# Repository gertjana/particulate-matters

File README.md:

# Particulate Matter Bike Monitor

This project is a mobile air quality monitoring system designed to be mounted on a bicycle. It measures fine particulate matter (PM1, PM2.5, and PM10) and records GPS location data during your commute. The collected data is stored locally on an SD card and displayed in real-time on an OLED screen, enabling you to create heatmaps of air pollution along your cycling routes.

## Features

- **Real-time air quality monitoring:** Measures PM1, PM2.5, and PM10 concentrations using the BMV080 particulate matter sensor.
- **GPS tracking:** Captures latitude, longitude, and timestamp for each measurement.
- **Local data storage:** Saves measurements to SD card with date-based file organization.
- **Real-time display:** Shows current readings and GPS coordinates on an OLED display.
- **Sensor health monitoring:** Detects when the sensor is obstructed and displays warnings.

## Hardware Requirements

- Arduino-compatible board (ESP32 recommended for SD card support)
- BMV080 Particulate Matter Sensor (I2C)
- GPS module (compatible with TinyGPS++)
- OLED Display (SSD1306, 128x32)
- SD Card Module (SPI)
- Battery pack
- Bicycle mounting hardware

## Pin Configuration

- **I2C (Wire):** SDA, SCL - for BMV080 sensor and OLED display
- **SPI (SD Card):** CS:44, MOSI:9, MISO:8, CLK:7
- **GPS (Software Serial):** TX:3, RX:2

## System Architecture

The system operates on a 10-second measurement interval and includes:

1. **Data Collection:** Reads PM1, PM2.5, PM10, and GPS coordinates
2. **Data Processing:** Packages data into JSON format
3. **Local Storage:** Saves to SD card with date-based filenames
4. **Real-time Display:** Shows current readings on OLED screen

## Data Format

Each measurement is stored as a JSON object with the following structure:

```json
{
  "pm": {
    "pm1": 15,
    "pm2.5": 25,
    "pm10": 45,
    "obstructed": false
  },
  "gps": {
    "date": "15-12-2024",
    "time": "14:30:25",
    "latitude": "52.12345678",
    "longitude": "4.87654321"
  }
}
```

## File Organization

Data is stored on the SD card with the following structure:

- Files are named by date: `DD-MM-YYYY.txt`
- Each line contains one JSON measurement
- Files are created automatically when data is available

## Setup

1. Clone this repository.
2. Install required libraries:
   - SparkFun_BMV080_Arduino_Library
   - TinyGPSPlus
   - ArduinoJson
   - Adafruit_GFX
   - Adafruit_SSD1306
3. Connect hardware according to pin configuration
4. Insert formatted SD card
5. Upload `dust_sensor_new/dust_sensor_new.ino` to your Arduino board
6. Mount the device on your bike and power it up before your ride

## Debug Mode

The system includes comprehensive debug output when `DEBUG` is defined. This includes:

- SD card information (type, size, free space)
- Sensor initialization status
- GPS data processing
- File writing operations

To enable debug mode, ensure `#define DEBUG` is uncommented in the code.

## Data Analysis

### Local Analysis

- Data files can be read directly from the SD card
- JSON format makes it easy to parse with any programming language
- Each measurement includes timestamp and location data

### Heatmap Generation

For setting up and using the heatmap visualization, see [heatmap/README.md](heatmap/README.md)

See [`example.md`](example.md) for sample data format and structure.

## License

MIT License

## Contributing

Contributions are welcome! Please open an issue or submit a pull request.

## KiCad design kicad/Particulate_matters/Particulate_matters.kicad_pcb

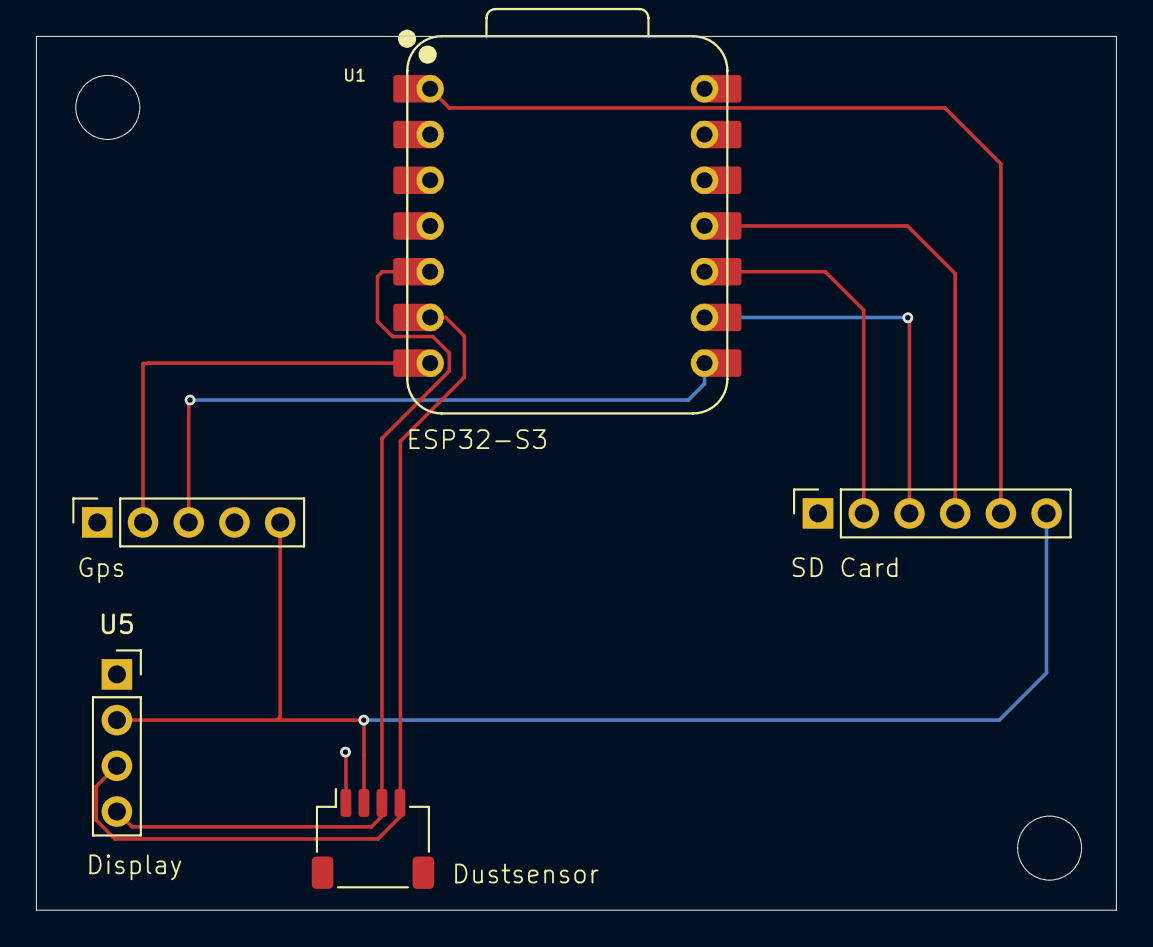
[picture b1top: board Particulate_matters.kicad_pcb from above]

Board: 2 copper layers, 60.0 x 48.5 mm, 5 parts (0 on the bottom side), 10 nets.

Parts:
U1: XIAO-ESP32-S3-DIP; XIAO-ESP32S3-DIP
U2: PinSocket_1x05_P2.54mm_Vertical
U3: JST_SH_SM04B-SRSS-TB_1x04-1MP_P1.00mm_Horizontal
U4: PinSocket_1x06_P2.54mm_Vertical
U5: PinSocket_1x04_P2.54mm_Vertical

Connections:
GND: U1.13 (GND), U2.4 (GND), U3.1 (GND), U4.1 (GND), U5.1 (GND)
unnamed: U1.1 (GPIO1/D0/A0), U4.5 (CS)
unnamed: U1.5 (GPIO5/D4/I2C_SDA), U3.3 (SDA), U5.4 (SDA)
unnamed: U1.9 (GPIO7/D8/A8/SCK), U4.3 (CLK)
unnamed: U1.10 (GPIO8/D9/A9/MISO), U4.2 (MISO)
unnamed: U1.6 (GPIO9/D5/I2C_SCL), U3.4 (SDL), U5.3 (SCK)
unnamed: U1.11 (GPIO9/D10/A10/MOSI), U4.4 (MOSI)
unnamed: U1.8 (U0RXD/D7/RX), U2.3 (TX)
unnamed: U1.7 (U0TXD/D6/TX), U2.2 (RX)
VCC: U1.12 (VCC_3V3), U2.5 (VCC), U3.2 (VCC), U4.6 (3V3), U5.2 (VCC)

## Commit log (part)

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2018-02-22 Arduino sketch to send ppd42 sensor data through lora
2018-03-11 added an gps module
2018-03-19 year is 2 bytes
2025-05-28 updated for new TTN Application and moved sensitive values out of the source
2025-06-02 All big endian now, added formatter to turn the data into json, and a markdown file describing the format
2025-06-03 Added altitude to the message instead of the centisecond
2025-06-03 Added temperature
2025-06-04 Removed Temperature, it was not needed in the calculations and took too much space in the box
2025-06-08 Split into measure and send parts, with a queue in between
2025-06-08 Added 3d files for the case modifications
2025-06-10 Added Readme, update example.md
2025-06-10 Cleanup
2025-06-24 Added Kicad Project
2025-06-25 Added a python script to generate heatmap's from the messages
2025-06-25 ignoring json messages and resulting html's
2025-06-25 Updated readme, heatmap has a legend and SF12 for the lora communication
2025-07-06 New version with XIAO ESP32S3, ATGM336H GPS and BMV080 PM Sensor
2025-07-06 Updated schematic and pcb design
2025-07-06 ignoring virtualenv stuff
2025-07-06 no such method
2025-07-10 updated pcb
2025-07-10 added soem d2 diagrams
2025-07-10 ignring kicad locks and backups
2025-07-10 AI updated version in _fixed.ino, readme now uses the svg diagram
